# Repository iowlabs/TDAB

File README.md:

# Tremor Detection Adquisition Board

This device developed is an acquisition board for reading biometric signals from the human body, such as an EEG or EMG.

The board is based on the ADS1299, a 24-bit low-noise analog-to-digital converter developed for applications working with biopotential signals. The board uses a Teensy 4.1 as a DSP microcontroller to perform the tasks of synchronization, parameter configuration, ADC reading, and communication with the host.

The main feature of this equipment is that it has 6 analog signal conditioning channels that are fully configurable by software.

Each channel implements a band-pass filter whose gain and cut-off frequencies can be configured. The band-pass filter is implemented by two independent filters in cascade, one high-pass and one low-pass.

## Features
- 1ksps sampling rate
- 6 independent operating channels
- Bandpass configurable filter
	- Configurable lower cutoff frequency between 0.5Hz and 50Hz.
	- Gonfigurable upper cutoff frequency between 100Hz and 10kHz.
	- Configurable channel gain.
- Software-configurable channels
- 24-bit ADC and sampling rate up to 16kHz
- 16-bit accelerometer reading and up to 200g 9DoF
- Real-time reading and data display interface.

## LICENSES

| Item     | License 	|
|----------|------------|
| Hardware | CERN-OHL-S-2.0 |
| Software | GPL-3.0-or-later|
| Firmware | GPL-3.0-or-later|
| Documentation | CC-BY-SA-4.0|

## Hardware description

## Electrónics

### Schematics

### Layout

### BOM

## 3D Model

## Firmware

## Software

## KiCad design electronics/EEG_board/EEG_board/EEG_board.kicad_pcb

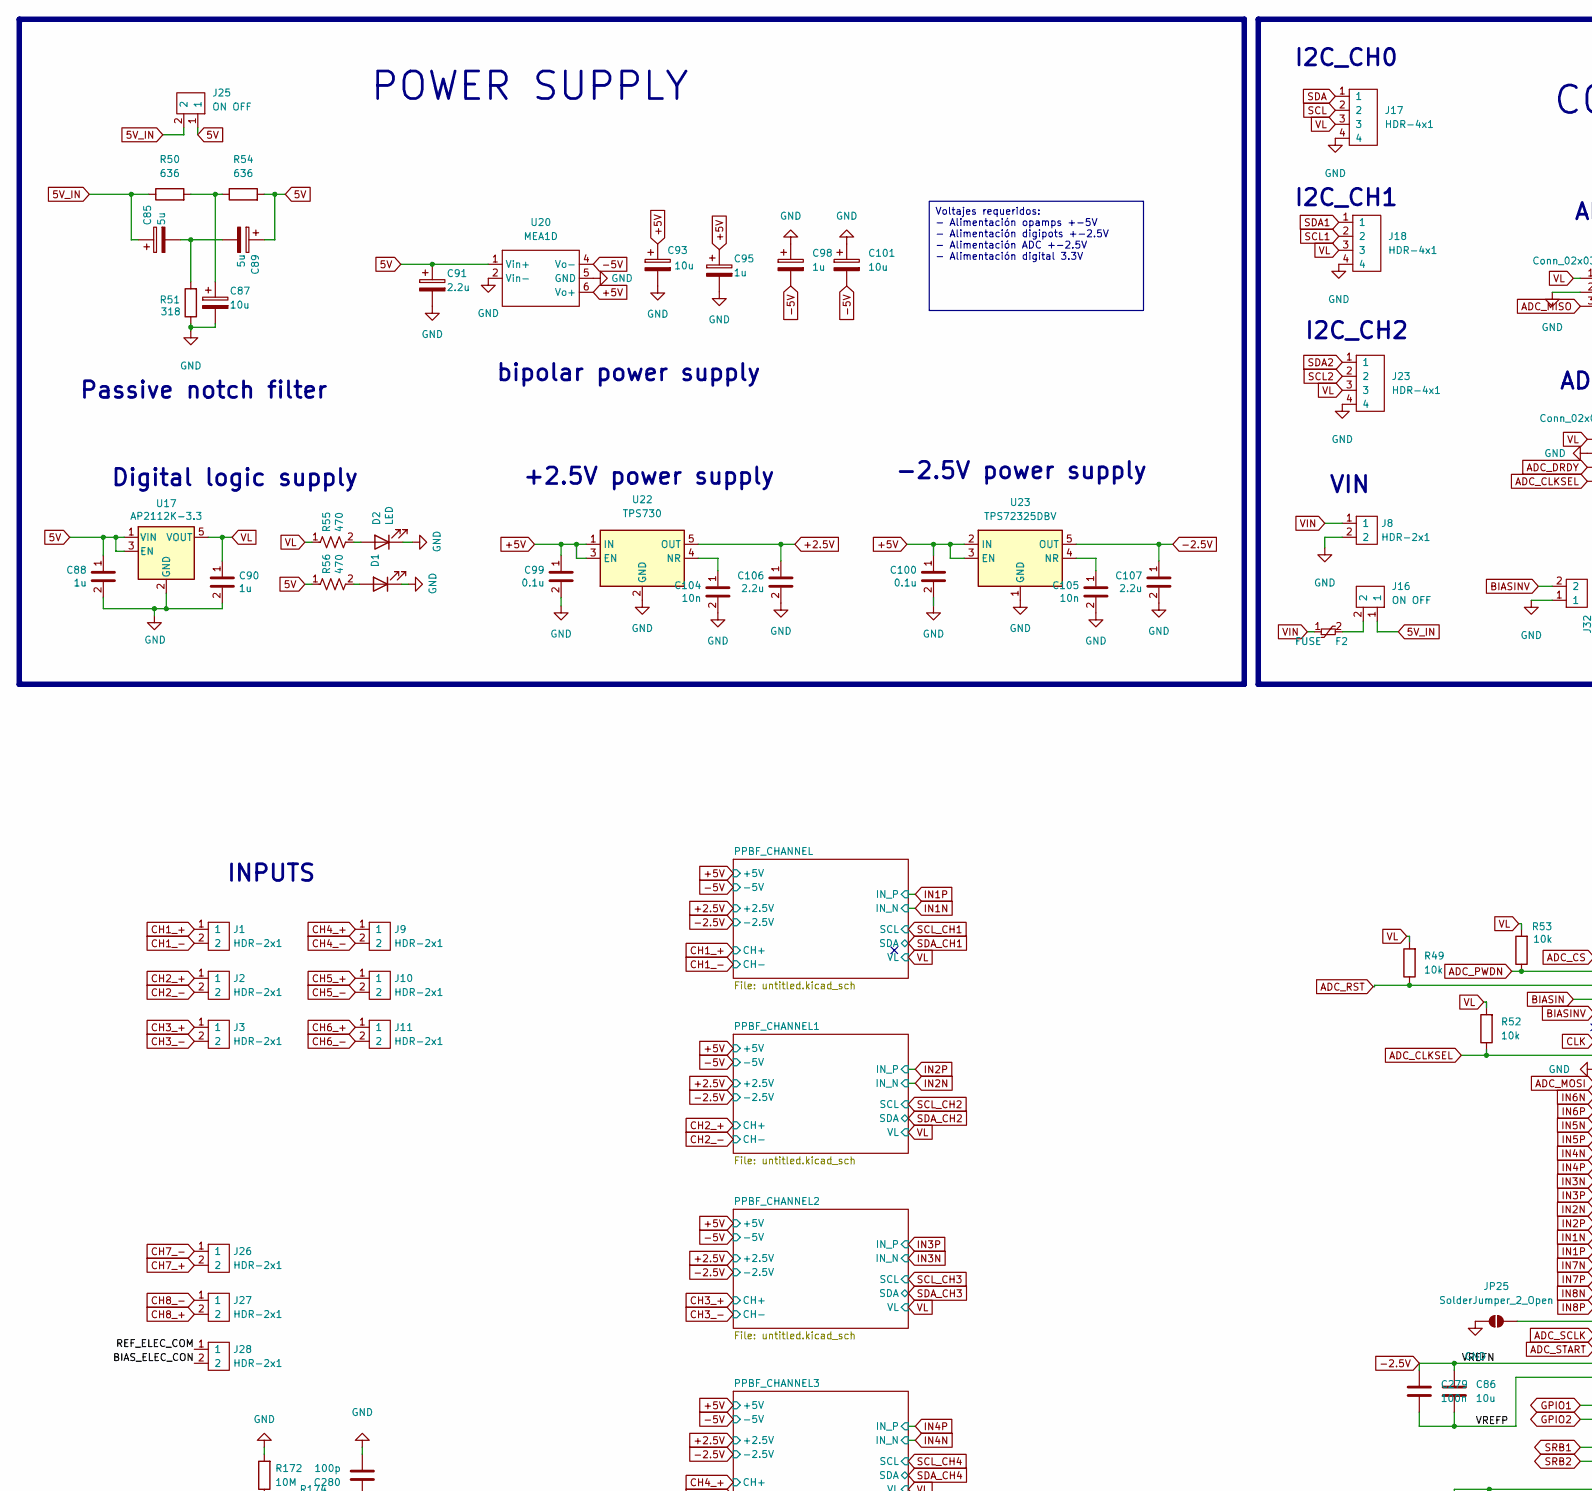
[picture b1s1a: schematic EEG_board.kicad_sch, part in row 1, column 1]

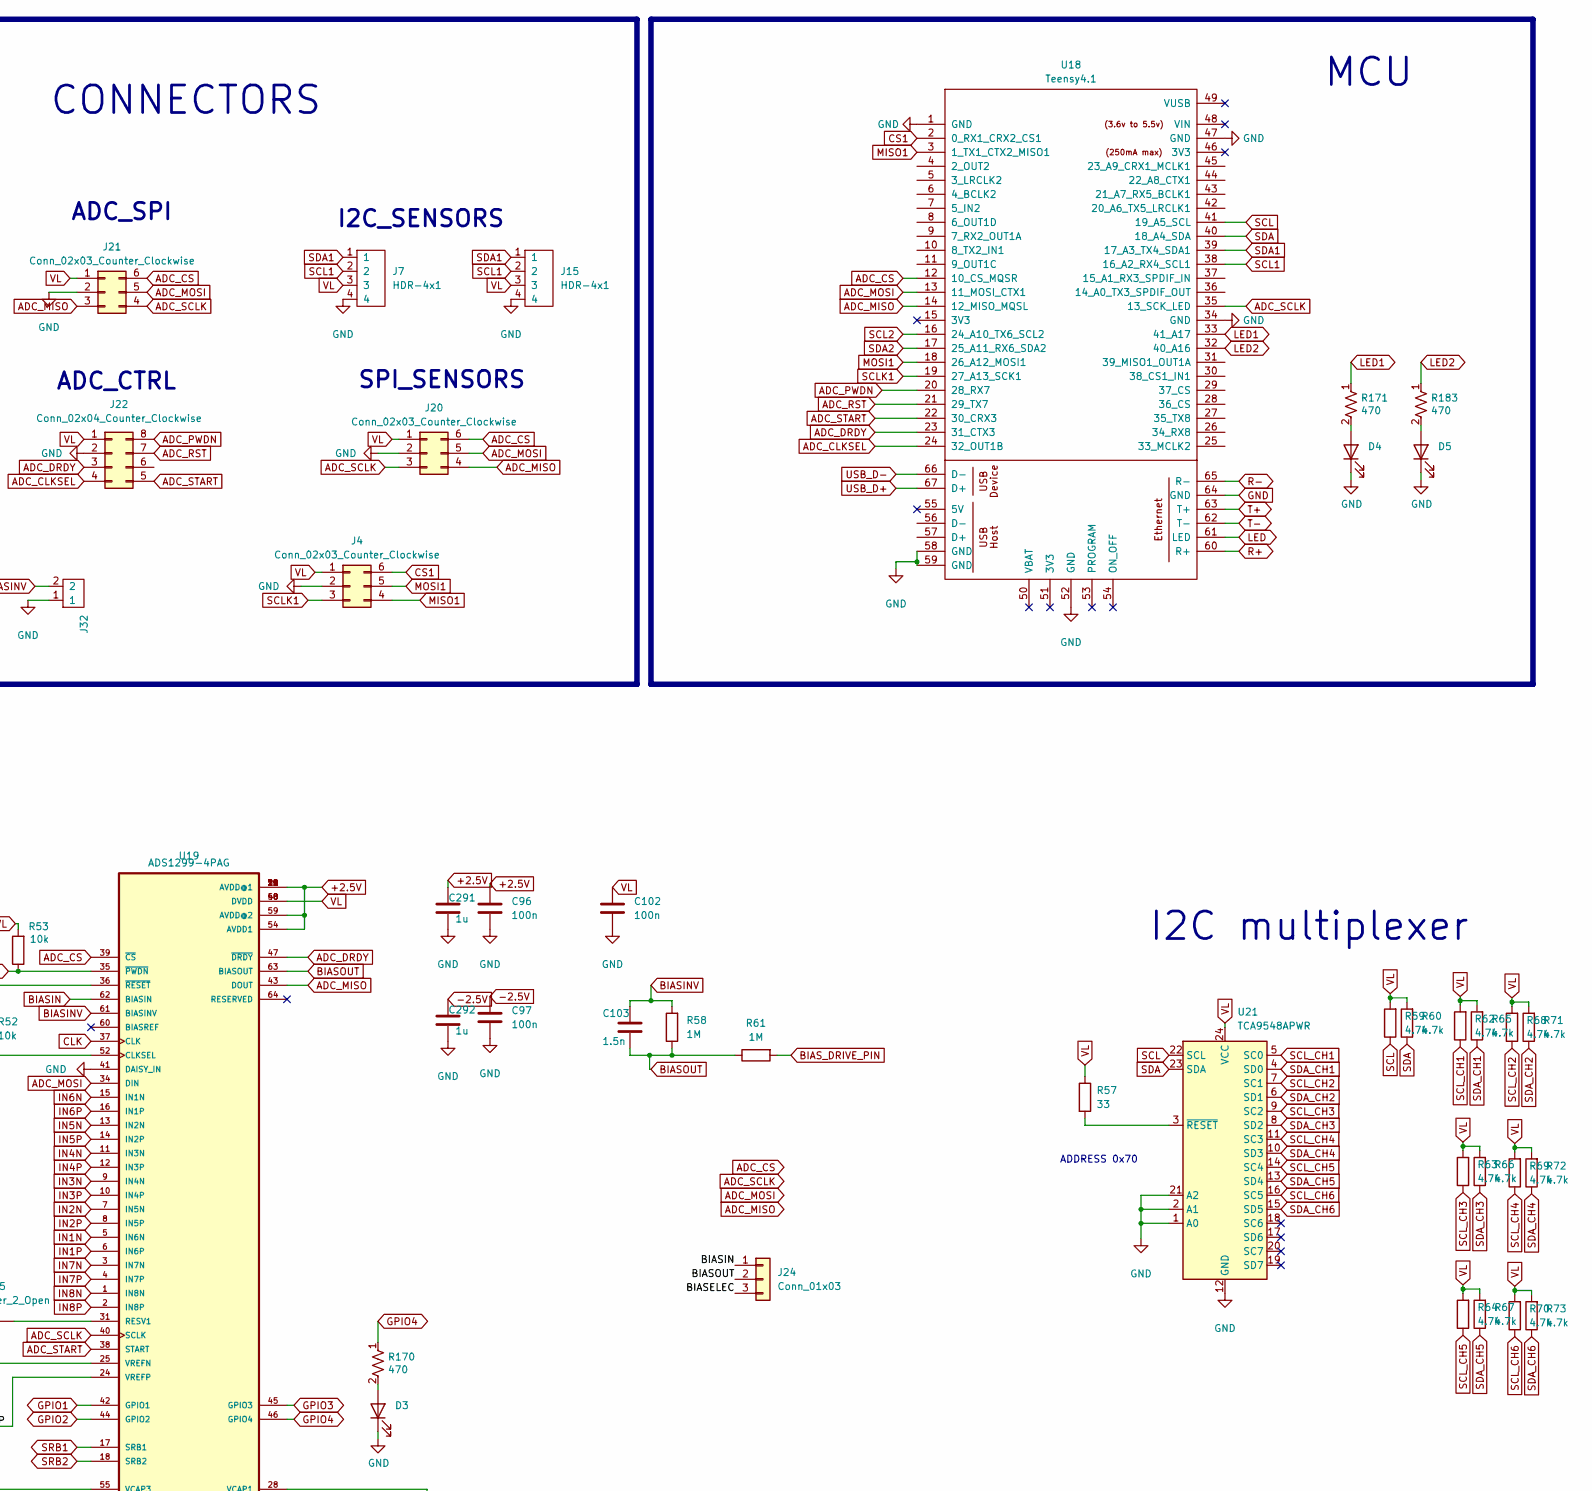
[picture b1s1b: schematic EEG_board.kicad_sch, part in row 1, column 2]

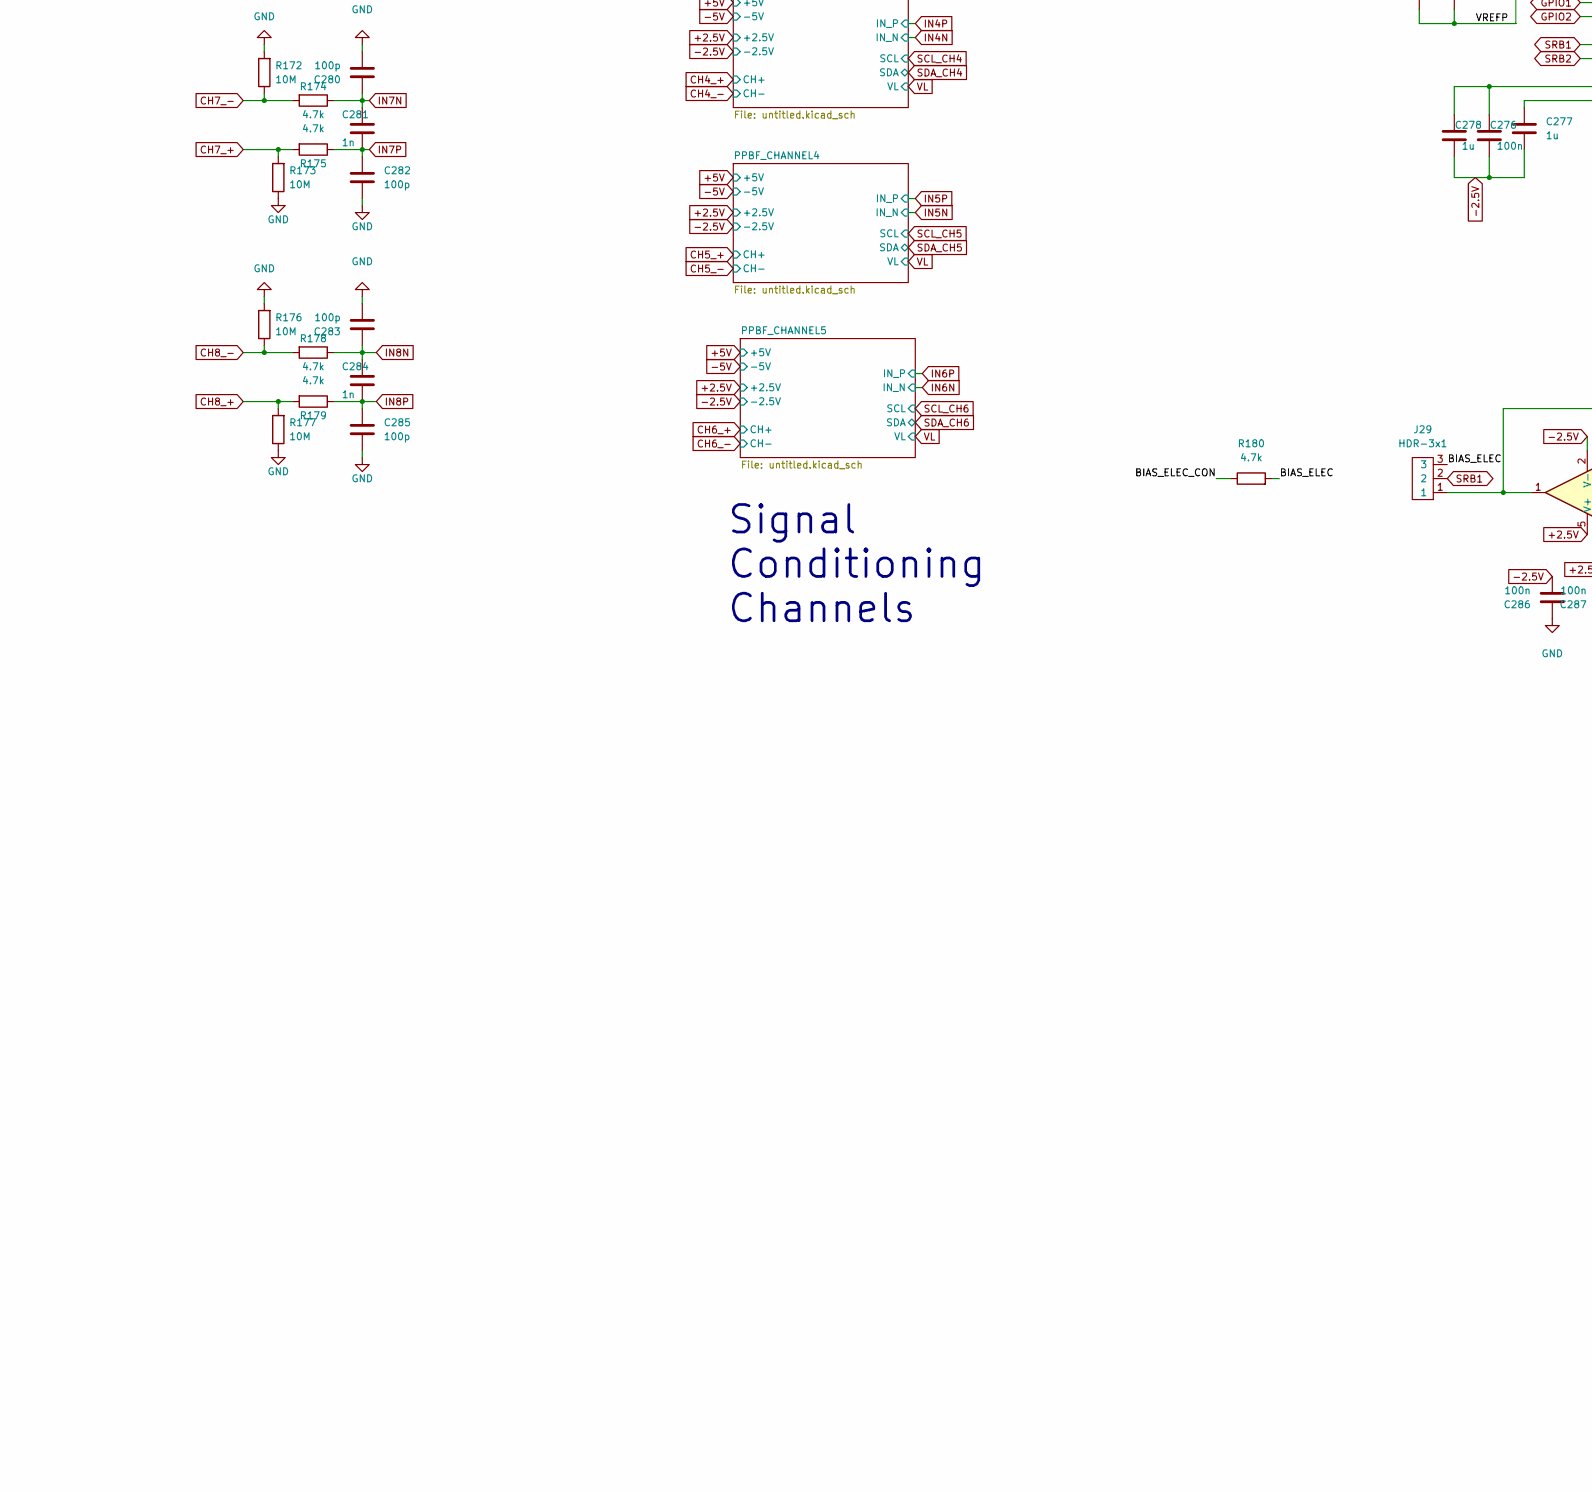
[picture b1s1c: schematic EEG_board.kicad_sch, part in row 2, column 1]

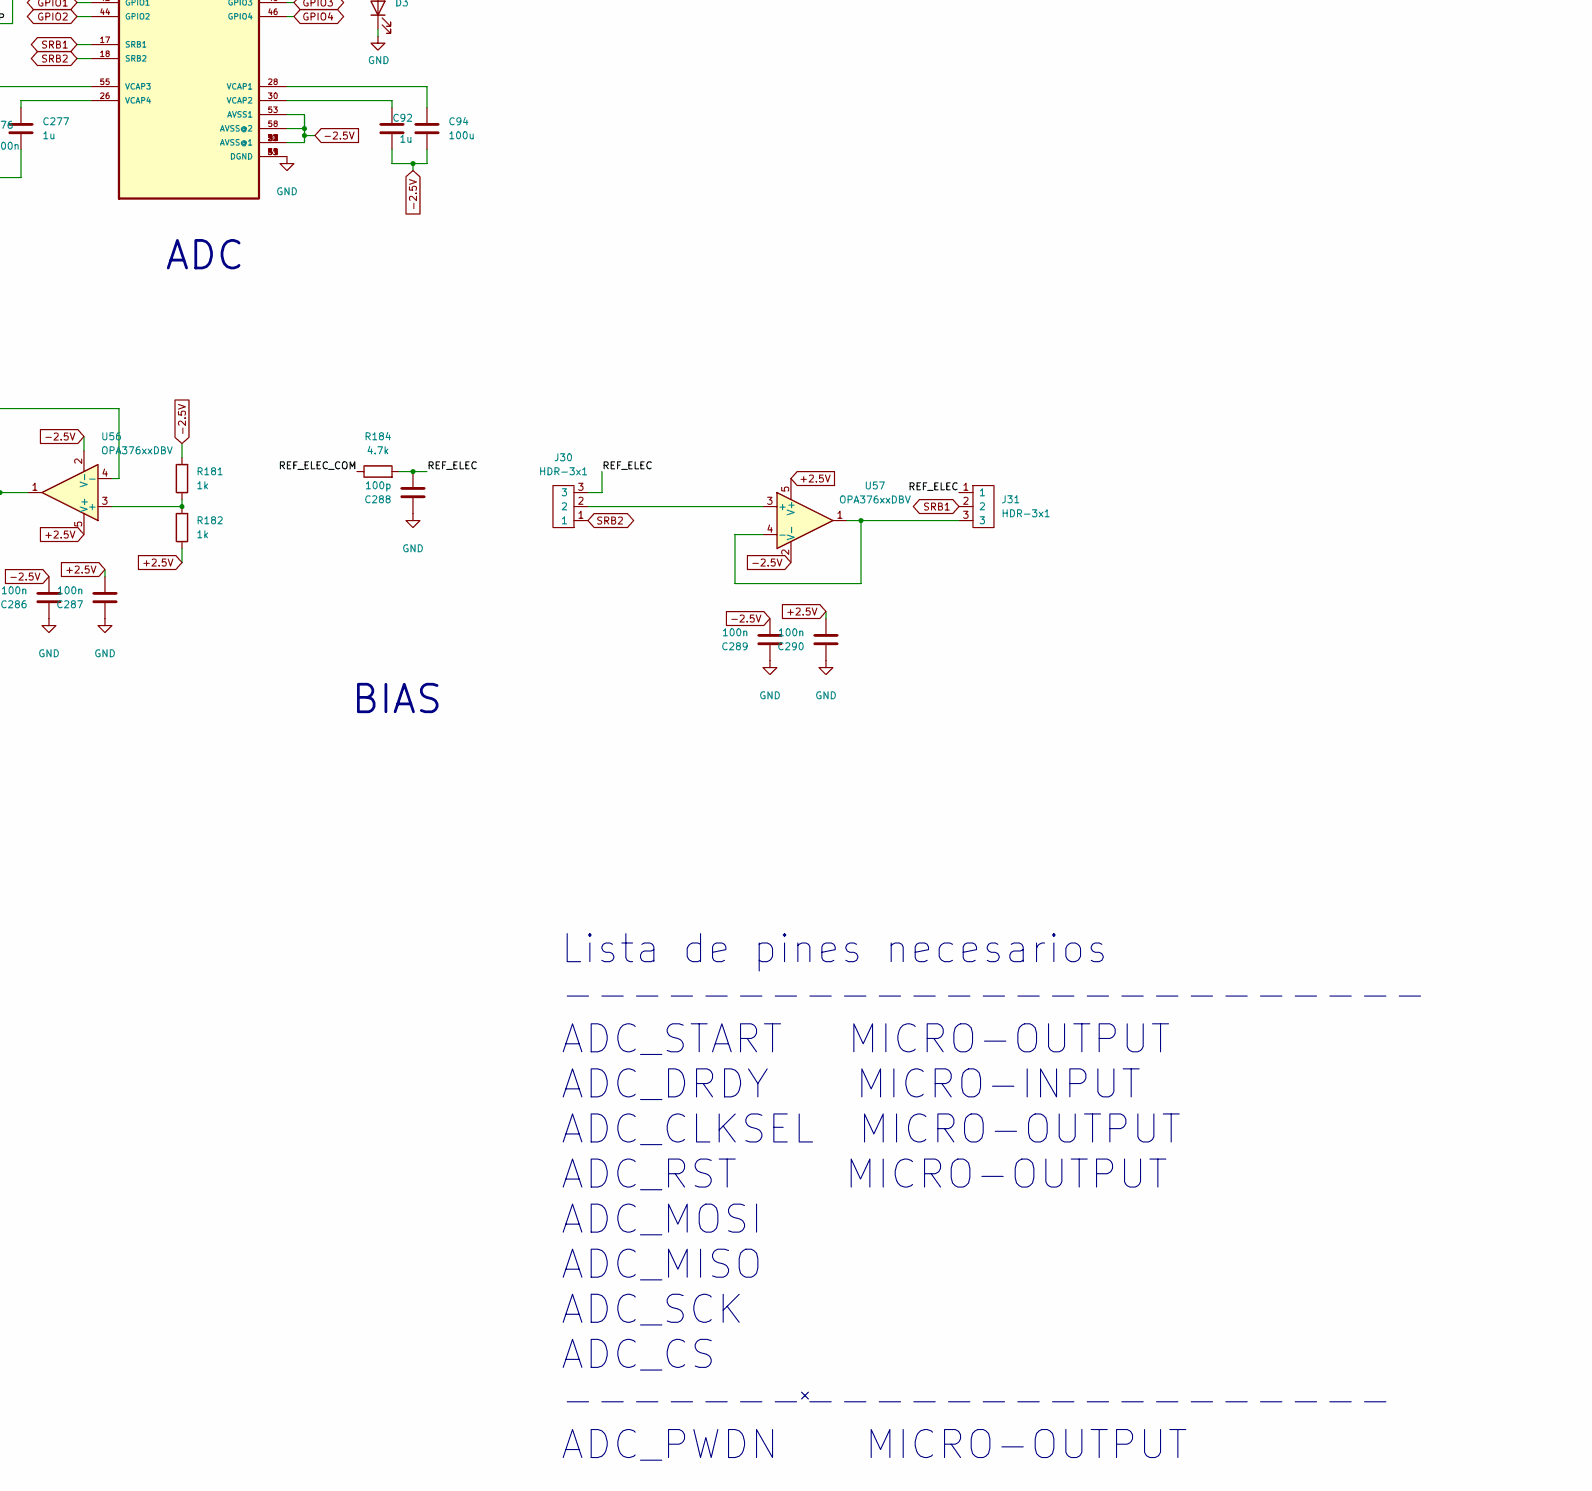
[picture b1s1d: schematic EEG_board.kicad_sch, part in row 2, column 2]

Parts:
C85, C89: 5u; CP_Elec_5x5.4
C86: 10u; C_0805_2012Metric
C87: 10u; CP_Elec_5x5.4
C88, C90: 1u; C_0805_2012Metric; Voltage rated 16V
C91: 2.2u; CP_Elec_4x5.3
C92, C277, C278, C291, C292: 1u; C_0805_2012Metric
C93, C101: 10u; CP_Elec_4x5.3
C94: 100u; C_0805_2012Metric
C95, C98: 1u; CP_Elec_4x5.3
C96, C97, C102, C276, C279, C286, C287, C289, C290: 100n; C_0603_1608Metric
C99, C100: 0.1u; C_0603_1608Metric; Voltage rated 16V
C103: 1.5n; C_0603_1608Metric
C104, C105: 10n; C_0603_1608Metric; Voltage rated 16V
C106, C107: 2.2u; C_0805_2012Metric; Voltage rated 16V
C280, C282, C283, C285, C288: 100p; C_0603_1608Metric
C281, C284: 1n; C_0603_1608Metric
D1, D2, D3, D4, D5: LED; LED_0603_1608Metric
F2: FUSE; Fuse_1206_3216Metric
J1, J2, J3, J9, J10, J11: HDR-2x1; JST-XH-2x1-2.5p-TH-V
J4, J21: Conn_02x03_Counter_Clockwise; PinHeader_2x03_P2.54mm_Vertical
J7, J15, J17, J18, J23: HDR-4x1; JST-XH-4x1-2.5P-TH-V
J8: HDR-2x1; Tb-2x1-5p-TH-V
J16, J25: ON OFF; PinHeader_1x02_P2.54mm_Vertical
J20: Conn_02x03_Counter_Clockwise
J22: Conn_02x04_Counter_Clockwise; PinHeader_2x04_P2.54mm_Vertical
J24: Conn_01x03
J26, J27, J28: HDR-2x1; JST_XH_B2B-XH-A_1x02_P2.50mm_Vertical
J29, J30, J31: HDR-3x1; PinHeader_1x03_P2.54mm_Vertical
J32: PinHeader_1x02_P2.54mm_Vertical
JP25: SolderJumper_2_Open; SolderJumper-2_P1.3mm_Open_RoundedPad1.0x1.5mm
R49, R52, R53: 10k; R_0603_1608Metric
R50, R54: 636; R_1206_3216Metric
R51: 318; R_1206_3216Metric
R55, R56, R170, R171, R183: 470; R_0603_1608Metric
R57: 33; R_0603_1608Metric
R58, R61: 1M; R_0603_1608Metric
R59, R60, R62, R63, R64, R65, R66, R67, R68, R69, R70, R71, R72, R73, R174, R175, R178, R179, R180, R184: 4.7k; R_0603_1608Metric
R172, R173, R176, R177: 10M; R_0603_1608Metric
R181, R182: 1k; R_0603_1608Metric
U17: AP2112K-3.3; SOT-23-5
U18: Teensy4.1; Teensy41
U19: ADS1299-4PAG; TQFP-64_10x10mm_P0.5mm
U20: MEA1D; Miniature SIP 6p
U21: TCA9548APWR; TSSOP-24_4.4x7.8mm_P0.65mm
U22: TPS730; SOT-23-5
U23: TPS72325DBV; SOT-23-5
U56, U57: OPA376xxDBV; SOT-23-5

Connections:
5V: C88.1, C89.1, C91.1, J25.1, R54.2, R56.1, U17.1 (VIN), U17.3 (EN), U20.1 (Vin+)
5V_IN: C85.1, J16.1, J25.2, R50.1
+2.5V: C96.1, C106.1, C287.2, C290.2, C291.1, R182.1, U19.19 (AVDD@1), U19.21 (AVDD@1), U19.22 (AVDD@1), U19.54 (AVDD1), U19.56 (AVDD@1), U19.59 (AVDD@2), U22.5 (OUT), U56.5 (V+), U57.5 (V+); also elsewhere on the board
+5V: C93.1, C95.1, C99.1, C100.1, U20.6 (Vo+), U22.1 (IN), U22.3 (EN), U23.2 (IN), U23.3 (EN); also elsewhere on the board
-2.5V: C86.1, C92.2, C94.2, C97.1, C107.1, C276.2, C277.2, C278.2, C279.1, C286.2, C289.2, C292.1, R181.2, U19.20 (AVSS@1), U19.23 (AVSS@1), U19.25 (VREFN), U19.32 (AVSS@1), U19.53 (AVSS1), U19.57 (AVSS@1), U19.58 (AVSS@2), U23.5 (OUT), U56.2 (V-), U57.2 (V-); also elsewhere on the board
-5V: C98.2, C101.2, U20.4 (Vo-); also elsewhere on the board
/BIAS_ELEC: J29.3, R180.2
/BIAS_ELEC_CON: J28.2, R180.1
/REF_ELEC: C288.2, J30.3, J31.1, R184.2
/REF_ELEC_COM: J28.1, R184.1
/VREFP: C86.2, C279.2, U19.24 (VREFP)
ADC_CLKSEL: J22.4, R52.1, U18.24 (32_OUT1B), U19.52 (CLKSEL)
ADC_CS: J20.6, J21.6, U18.12 (10_CS_MQSR), U19.39 (~CS)
ADC_DRDY: J22.3, U18.23 (31_CTX3), U19.47 (~DRDY)
ADC_MISO: J20.4, J21.3, U18.14 (12_MISO_MQSL), U19.43 (DOUT)
ADC_MOSI: J20.5, J21.5, U18.13 (11_MOSI_CTX1), U19.34 (DIN)
ADC_PWDN: J22.8, R53.1, U18.20 (28_RX7), U19.35 (~PWDN)
ADC_RST: J22.7, R49.1, U18.21 (29_TX7), U19.36 (~RESET)
ADC_SCLK: J20.3, J21.4, U18.35 (13_SCK_LED), U19.40 (SCLK)
ADC_START: J22.5, U18.22 (30_CRX3), U19.38 (START)
BIASIN: U19.62 (BIASIN)
BIASINV: C103.1, J32.2, R58.2, U19.61 (BIASINV)
BIASOUT: C103.2, R58.1, R61.1, U19.63 (BIASOUT)
BIAS_DRIVE_PIN: R61.2
CH1_+: J1.1; also elsewhere on the board
CH1_-: J1.2; also elsewhere on the board
CH2_+: J2.1; also elsewhere on the board
CH2_-: J2.2; also elsewhere on the board
CH3_+: J3.1; also elsewhere on the board
CH3_-: J3.2; also elsewhere on the board
CH4_+: J9.1; also elsewhere on the board
CH4_-: J9.2; also elsewhere on the board
CH5_+: J10.1; also elsewhere on the board
CH5_-: J10.2; also elsewhere on the board
CH6_+: J11.1; also elsewhere on the board
CH6_-: J11.2; also elsewhere on the board
CH7_+: J26.2, R173.2, R175.2
CH7_-: J26.1, R172.1, R174.2
CH8_+: J27.2, R177.2, R179.2
CH8_-: J27.1, R176.1, R178.2
CLK: U19.37 (CLK)
CS1: J4.6, U18.2 (0_RX1_CRX2_CS1)
GND: C87.2, C88.2, C90.2, C91.2, C93.2, C95.2, C96.2, C97.2, C98.1, C99.2, C100.2, C101.1, C102.2, C104.2, C105.2, C106.2, C107.2, C280.2, C282.2, C283.2, C285.2, C286.1, C287.1, C288.1, C289.1, C290.1, C291.2, C292.2, D1.1 (K), D2.1 (K), D3.1 (K), D4.1 (K), D5.1 (K), J4.2, J7.4, J8.2, J15.4, J17.4, J18.4, J20.2, J21.2, J22.2, J23.4, J32.1, JP25.1 (A), R51.1, R172.2, R173.1, R176.2, R177.1, U17.2 (GND), U18.1 (GND), U18.34 (GND), U18.47 (GND), U18.52 (GND), U18.58 (GND), U18.59 (GND), U18.64 (GND), U19.33 (DGND), U19.41 (DAISY_IN), U19.49 (DGND), U19.51 (DGND), U20.2 (Vin-), U20.5 (GND), U21.1 (A0), U21.2 (A1), U21.12 (GND), U21.21 (A2), U22.2 (GND), U23.1 (GND); also elsewhere on the board
GPIO1: U19.42 (GPIO1)
GPIO2: U19.44 (GPIO2)
GPIO3: U19.45 (GPIO3)
GPIO4: R170.1, U19.46 (GPIO4)
IN1N: U19.5 (IN6N); also elsewhere on the board
IN1P: U19.6 (IN6P); also elsewhere on the board
IN2N: U19.7 (IN5N); also elsewhere on the board
IN2P: U19.8 (IN5P); also elsewhere on the board
IN3N: U19.9 (IN4N); also elsewhere on the board
IN3P: U19.10 (IN4P); also elsewhere on the board
IN4N: U19.11 (IN3N); also elsewhere on the board
IN4P: U19.12 (IN3P); also elsewhere on the board
IN5N: U19.13 (IN2N); also elsewhere on the board
IN5P: U19.14 (IN2P); also elsewhere on the board
IN6N: U19.15 (IN1N); also elsewhere on the board
IN6P: U19.16 (IN1P); also elsewhere on the board
IN7N: C280.1, C281.1, R174.1, U19.3 (IN7N)
IN7P: C281.2, C282.1, R175.1, U19.4 (IN7P)
IN8N: C283.1, C284.1, R178.1, U19.1 (IN8N)
IN8P: C284.2, C285.1, R179.1, U19.2 (IN8P)
LED: U18.61 (LED)
LED1: R171.1, U18.33 (41_A17)
LED2: R183.1, U18.32 (40_A16)
MISO1: J4.4, U18.3 (1_TX1_CTX2_MISO1)
MOSI1: J4.5, U18.18 (26_A12_MOSI1)
unnamed: C85.2, C89.2, R51.2
unnamed: C87.1, R50.2, R54.1
unnamed: D1.2 (A), R56.2
unnamed: D2.2 (A), R55.2
unnamed: D3.2 (A), R170.2
unnamed: D4.2 (A), R171.2
unnamed: D5.2 (A), R183.2
unnamed: F2.2, J16.2
unnamed: JP25.2 (B), U19.31 (RESV1)
unnamed: C94.1, U19.28 (VCAP1)
unnamed: C92.1, U19.30 (VCAP2)
unnamed: C276.1, C278.1, U19.55 (VCAP3)
unnamed: C277.1, U19.26 (VCAP4)
unnamed: R57.2, U21.3 (~RESET)
unnamed: C104.1, U22.4 (NR)
unnamed: C105.1, U23.4 (NR)
unnamed: R181.1, R182.2, U56.3 (+)
unnamed: J29.1, U56.1, U56.4 (-)
unnamed: J30.2, U57.3 (+)
unnamed: J31.3, U57.1, U57.4 (-)
R+: U18.60 (R+)
R-: U18.65 (R-)
SCL: J17.2, R59.1, U18.41 (19_A5_SCL), U21.22 (SCL)
SCL1: J7.2, J15.2, J18.2, U18.38 (16_A2_RX4_SCL1)
SCL2: J23.2, U18.16 (24_A10_TX6_SCL2)
SCLK1: J4.3, U18.19 (27_A13_SCK1)
SCL_CH1: R62.1, U21.5 (SC0); also elsewhere on the board
SCL_CH2: R68.1, U21.7 (SC1); also elsewhere on the board
SCL_CH3: R63.1, U21.9 (SC2); also elsewhere on the board
SCL_CH4: R69.1, U21.11 (SC3); also elsewhere on the board
SCL_CH5: R64.1, U21.14 (SC4); also elsewhere on the board
SCL_CH6: R70.1, U21.16 (SC5); also elsewhere on the board
SDA: J17.1, R60.1, U18.40 (18_A4_SDA), U21.23 (SDA)
SDA1: J7.1, J15.1, J18.1, U18.39 (17_A3_TX4_SDA1)
SDA2: J23.1, U18.17 (25_A11_RX6_SDA2)
SDA_CH1: R65.1, U21.4 (SD0); also elsewhere on the board
SDA_CH2: R71.1, U21.6 (SD1); also elsewhere on the board
SDA_CH3: R66.1, U21.8 (SD2); also elsewhere on the board
SDA_CH4: R72.1, U21.10 (SD3); also elsewhere on the board
SDA_CH5: R67.1, U21.13 (SD4); also elsewhere on the board
SDA_CH6: R73.1, U21.15 (SD5); also elsewhere on the board
SRB1: J29.2, J31.2, U19.17 (SRB1)
SRB2: J30.1, U19.18 (SRB2)
T+: U18.63 (T+)
T-: U18.62 (T-)
USB_D+: U18.67 (D+)
USB_D-: U18.66 (D-)
VIN: F2.1, J8.1
VL: C90.1, C102.1, J4.1, J7.3, J15.3, J17.3, J18.3, J20.1, J21.1, J22.1, J23.3, R49.2, R52.2, R53.2, R55.1, R57.1, R59.2, R60.2, R62.2, R63.2, R64.2, R65.2, R66.2, R67.2, R68.2, R69.2, R70.2, R71.2, R72.2, R73.2, U17.5 (VOUT), U19.48 (DVDD), U19.50 (DVDD), U21.24 (VCC); also elsewhere on the board

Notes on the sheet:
Voltajes requeridos: - Alimentación opamps +-5V - Alimentación digipots +-2.5V - Alimentación ADC +-2.5V - Alimentación digital 3.3V
I2C multiplexer
Digital logic supply
ADC
MCU
I2C_CH2
-2.5V power supply
ADDRESS 0x70
SPI_SENSORS
CONNECTORS
POWER SUPPLY
bipolar power supply
Signal Conditioning Channels
Lista de pines necesarios ------------------------- ADC_START MICRO-OUTPUT ADC_DRDY MICRO-INPUT ADC_CLKSEL MICRO-OUTPUT ADC_RST MICRO-OUTPUT ADC_MOSI ADC_MISO ADC_SCK ADC_CS ------------------------ ADC_PWDN MICRO-OUTPUT
I2C_CH1
Passive notch filter
BIAS
+2.5V power supply
ADC_SPI
VIN
I2C_CH0
INPUTS
ADC_CTRL
I2C_SENSORS
